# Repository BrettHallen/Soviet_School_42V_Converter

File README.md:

# Soviet School 42V Converter
Convert Australian 230VAC power to Soviet 42VAC for computers & calculators.<br>

The Soviet had a low-voltage (42V) power supply available that used a special plug & socket (розетка 42В).<br>

This was used by calculators such as the «Электроника МКШ-2» and computers such as the «Электроника МС0511».<br>

This appears similar to the Clipsal 402/32 (socket) and 492/32 (plug) available in Australia for low voltage requirements.<br>

My idea was to create a simple 230VAC-to-42VAC step-down power supply with matching socket.<br>

My initial design will be using the Triad Magentics FP40-600 transformer.<br>

I'm not sure if the Soviet plug will fit the Australian socket, but the plug can always be replaced.<br>

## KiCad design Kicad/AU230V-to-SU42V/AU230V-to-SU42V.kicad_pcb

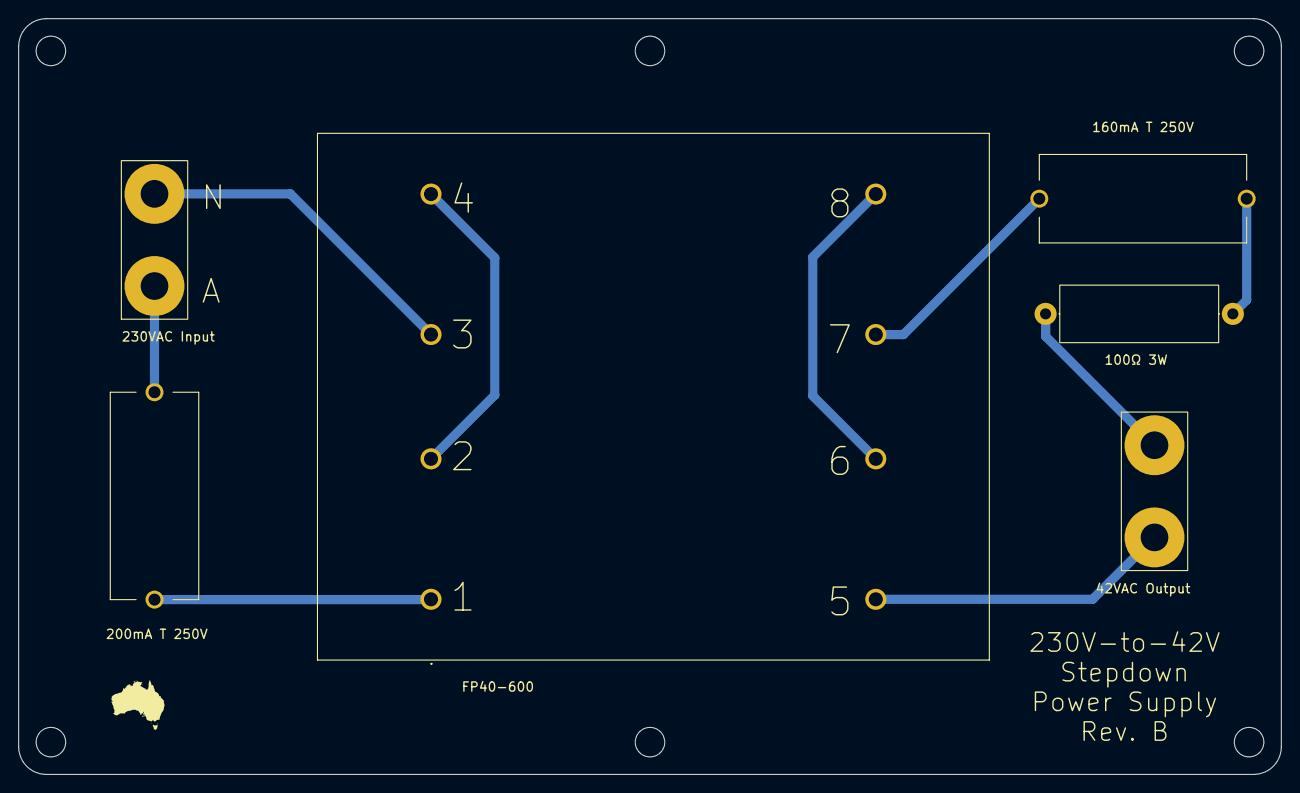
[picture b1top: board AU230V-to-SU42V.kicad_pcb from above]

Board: 2 copper layers, 137.0 x 82.0 mm, 12 parts (0 on the bottom side), 9 nets.

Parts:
F1: 200mA T 250V; Littelfuse_5x20mm
F2: 160mA T 250V; Littelfuse_5x20mm
H1, H2, H3, H4, H5, H6: MountingHole; MountingHole_3.2mm_M3
J1: 230VAC Input; TJC1-2A
J2: 42VAC Output; TJC1-2A
R1: 100Ω 3W; R_Axial_DIN0617_L17.0mm_D6.0mm_P20.32mm_Horizontal
T1: FP40-600; FP40600

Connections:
/42V_A: J2.1, T1.5 (SEC_A_S)
/42V_B: F2.1, T1.8 (SEC_B_F)
/230V_A: F1.1, J1.1 (L)
/230V_N: J1.2 (N), T1.4 (PRI_B_F)
unnamed: F2.2, R1.1
unnamed: J2.2, R1.2
unnamed: T1.2 (PRI_A_F), T1.3 (PRI_B_S)
unnamed: F1.2, T1.1 (PRI_A_S)
unnamed: T1.6 (SEC_A_F), T1.7 (SEC_B_S)
